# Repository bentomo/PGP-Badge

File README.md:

# Pokemon Go Plus Custom Badge

## Installing Toolchain

This was all tested under Windows 10

1. Install Python 2.7 (This is tested by 2.7.12)
	This is required for the edf-sdk installer

2. Install CMake for Windows (Tested using 3.17.0)

3. Install espressif SDK (Tested using Windows installer 2.2)
https://docs.espressif.com/projects/esp-idf/en/latest/get-started/#id1

I needed to use this because of an installer problem
https://github.com/espressif/esp-idf/issues/4744

`python.exe -m pip install --upgrade virtualenv==16.7.9`

Then run the program as administrator

## Extracting a MAC, Blob, and Key

Note that this is unusable without a Mac address, BLOB and device key from an **ORIGINAL** Pokemon GO plus
Pokeball plus and Gotcha not supported
https://github.com/Jesus805/Suota-Go-Plus

It's easiest to use the release page app 

Currently the app is bugged, it can download custom firmware but you need to use the  nRF android app to extract the values and restore the FW
MAC address is given by the app
characteristic `870d5ab1-20bd-b88a-5746-a97f5c33ea58` is the device key
characteristic `fe0002af-f8e3-f1b2-b141-b40adf381d18` is the blob

To restore the FW

1. Write 0x01 to Characteristic `6b64be6f-5467-d8b5-7143-1716be1b96be`
2. Disconnect from the device
3. Wait a few seconds
4. Press the Pokemon Go Plus button, it should be flashing blue or white

## Building the firmware

1. Open a command window
2. Browse to the esp-idf folder and run export.bat to setup sdk
3. Browse to the pgpemu-esp32 project folder and run `idf.py menuconfig`
4. Exit using the default configuration
5. Modify your secrets.c file with your MAC, Blob, and Key extracted from an original Pokemon GO Plus - This file is not tracked by git
6. Build the firmware using `idf.py build`
7. Flash the firmware using `idf.py -p (PORT) flash` where (PORT) is the COMX that the esp32 enumerated as

For more background read:
http://tinyhack.com/2018/11/21/reverse-engineering-pokemon-go-plus/

## Preliminary parts list
> ESP32 - Bluetooth - https://www.digikey.com/product-detail/en/espressif-systems/ESP32-WROOM-32/1904-1010-1-ND/8544305
> SSD1306 - OLED LCD - https://www.amazon.com/WINGONEER-Display-SSD1306-Headers-Arduino/dp/B07QB65CPS/ref=sr_1_5?keywords=oled+module&qid=1584226742&sr=8-5
> ~~ adafruit 1578 - 500mah battery - https://www.digikey.com/product-detail/en/adafruit-industries-llc/1578/1528-1841-ND/5054539 ~~
> battery - https://www.digikey.com/product-detail/en/tinycircuits/ASR00008/1832-1044-ND/8680974
> BQ27426 - Fuel Gauge - https://www.digikey.com/product-detail/en/texas-instruments/BQ27426YZFR/296-43359-1-ND/5806500
> LM3658 - Battery Charger - https://www.digikey.com/product-detail/en/texas-instruments/LM3658SD-NOPB/LM3658SD-NOPBCT-ND/808013
> TPS63030 - Voltage Regulator - https://www.digikey.com/product-detail/en/texas-instruments/TPS63030DSKR/296-39460-1-ND/5143408
> CP2102N - USB Interface - https://www.digikey.com/product-detail/en/silicon-labs/CP2102N-A01-GQFN20R/336-4826-1-ND/8619802
> USB4085 - Through hole usb c - https://www.digikey.com/product-detail/en/gct/USB4085-GF-A/2073-USB4085-GF-ACT-ND/9859733
> 316040004 - Vibration Motor - https://www.digikey.com/product-detail/en/seeed-technology-co-ltd/316040004/1597-1245-ND/5487673
> ~~ BQ297X - Protection Circuit - http://www.ti.com/lit/ds/symlink/bq2971.pdf ~ Battery includes protection circuit~

Other components not listed
jelly beans
sense resitors
tactile switches
mechanicals

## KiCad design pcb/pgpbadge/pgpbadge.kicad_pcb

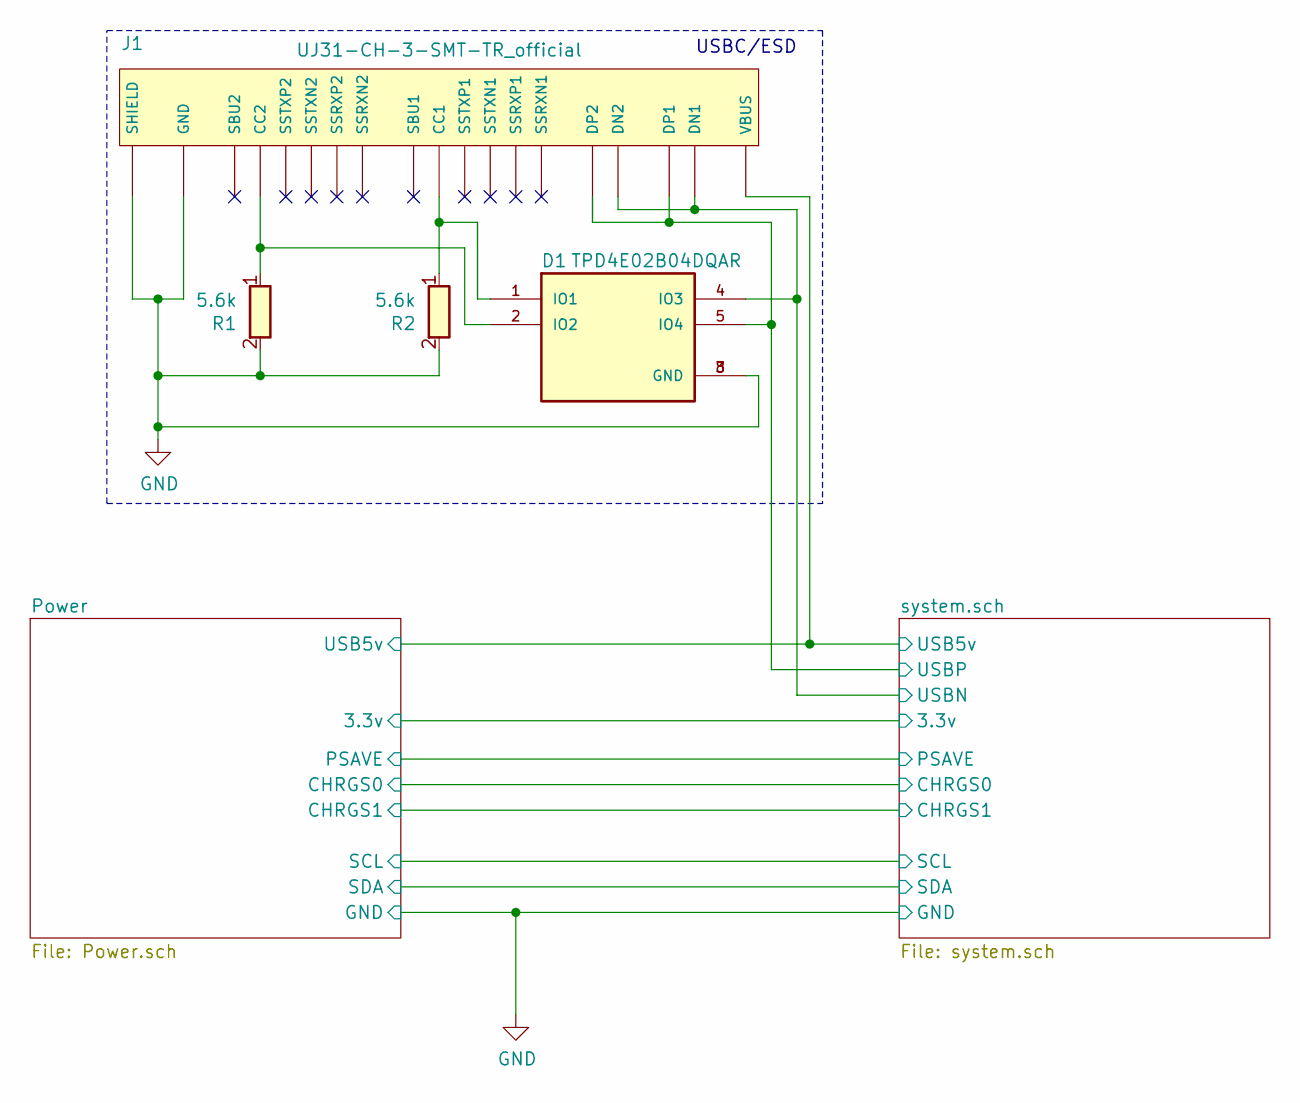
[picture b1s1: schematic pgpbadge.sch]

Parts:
D1: TPD4E02B04DQAR; DIO_TPD4E02B04DQAR
J1: UJ31-CH-3-SMT-TR_official; CUI_UJ31-CH-3-SMT-TR
R1, R2: 5.6k; R_0402_1005Metric

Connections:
/Power/USB5v: J1.A4 (VBUS), J1.A9 (VBUS), J1.B4 (VBUS), J1.B9 (VBUS); also elsewhere on the board
/system.sch/USBN: D1.4 (IO3), J1.A7 (DN1), J1.B7 (DN2); also elsewhere on the board
/system.sch/USBP: D1.5 (IO4), J1.A6 (DP1), J1.B6 (DP2); also elsewhere on the board
GND: D1.3 (GND), D1.8 (GND), J1.0 (SHIELD), J1.A1 (GND), J1.A12 (GND), J1.B1 (GND), J1.B12 (GND), R1.2, R2.2; also elsewhere on the board
unnamed: D1.1 (IO1), J1.A5 (CC1), R2.1
unnamed: D1.2 (IO2), J1.B5 (CC2), R1.1

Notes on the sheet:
USBC/ESD

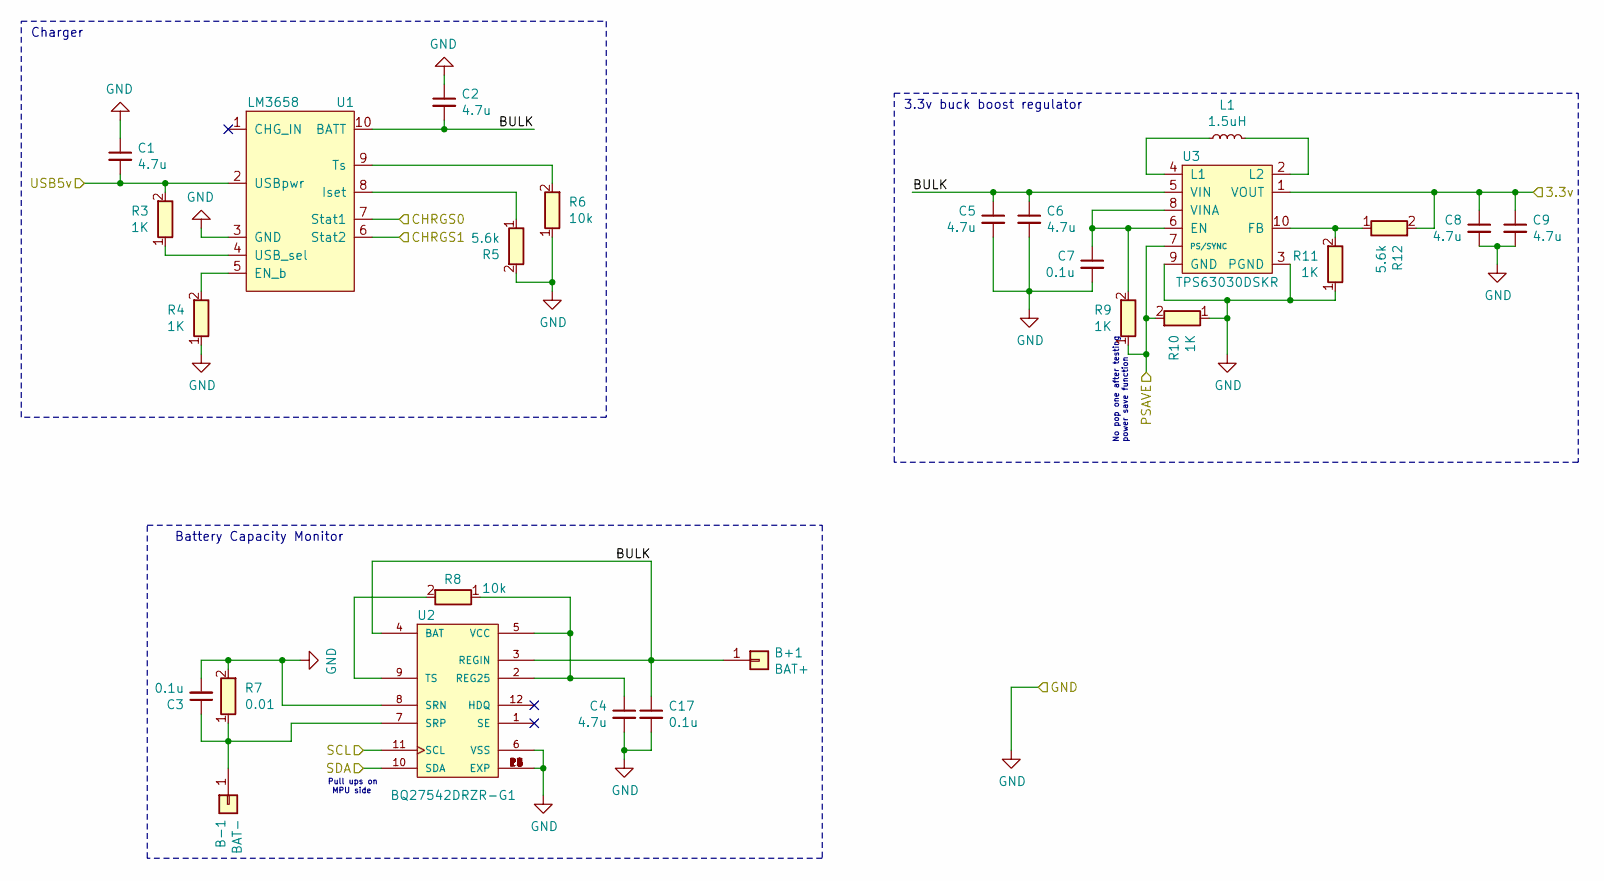
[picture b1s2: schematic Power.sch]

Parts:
B+1: BAT+; solder_pad
B-1: BAT-; solder_pad
C1, C2, C4, C5, C6, C8, C9: 4.7u; C_0805_2012Metric
C3, C7, C17: 0.1u; C_0402_1005Metric
L1: 1.5uH; L_1008_2520Metric
R3, R4, R9, R10, R11: 1K; R_0402_1005Metric
R5, R12: 5.6k; R_0402_1005Metric
R6, R8: 10k; R_0402_1005Metric
R7: 0.01; R_1206_3216Metric
U1: LM3658; wson-10-3x3
U2: BQ27542DRZR-G1; SON40P250X400X100-13N
U3: TPS63030DSKR; 10-WFDFN_EP_2.5_2.5

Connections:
/Power/BULK: B+1.1, C2.2, C5.1, C6.1, C17.1, U1.10 (BATT), U2.3 (REGIN), U2.4 (BAT), U3.5 (VIN)
/Power/CHRGS0: U1.7 (Stat1); also elsewhere on the board
/Power/CHRGS1: U1.6 (Stat2); also elsewhere on the board
/Power/PSAVE: R9.1, R10.2, U3.7 (PS/SYNC); also elsewhere on the board
/Power/SCL: U2.11 (SCL); also elsewhere on the board
/Power/SDA: U2.10 (SDA); also elsewhere on the board
/Power/USB5v: C1.2, R3.2, U1.2 (USBpwr); also elsewhere on the board
GND: C1.1, C2.1, C3.2, C4.2, C5.2, C6.2, C7.2, C8.2, C9.2, C17.2, R4.1, R5.2, R6.1, R7.2, R10.1, R11.1, U1.3 (GND), U2.6 (VSS), U2.8 (SRN), U2.13 (EXP), U2.14 (EXP), U2.15 (EXP), U2.P1 (EXP), U2.P2 (EXP), U2.P3 (EXP), U2.P4 (EXP), U2.P5 (EXP), U2.P6 (EXP), U3.3 (PGND), U3.9 (GND); also elsewhere on the board
unnamed: B-1.1, C3.1, R7.1, U2.7 (SRP)
unnamed: C4.1, R8.1, U2.2 (REG25), U2.5 (VCC)
unnamed: C7.1, R9.2, U3.6 (EN), U3.8 (VINA)
unnamed: L1.1, U3.4 (L1)
unnamed: L1.2, U3.2 (L2)
unnamed: R3.1, U1.4 (USB_sel)
unnamed: R4.2, U1.5 (EN_b)
unnamed: R5.1, U1.8 (Iset)
unnamed: R6.2, U1.9 (Ts)
unnamed: R8.2, U2.9 (TS)
unnamed: R11.2, R12.1, U3.10 (FB)

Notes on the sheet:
Pull ups on MPU side
No pop one after testing power save function
3.3v buck boost regulator
Battery Capacity Monitor
Charger

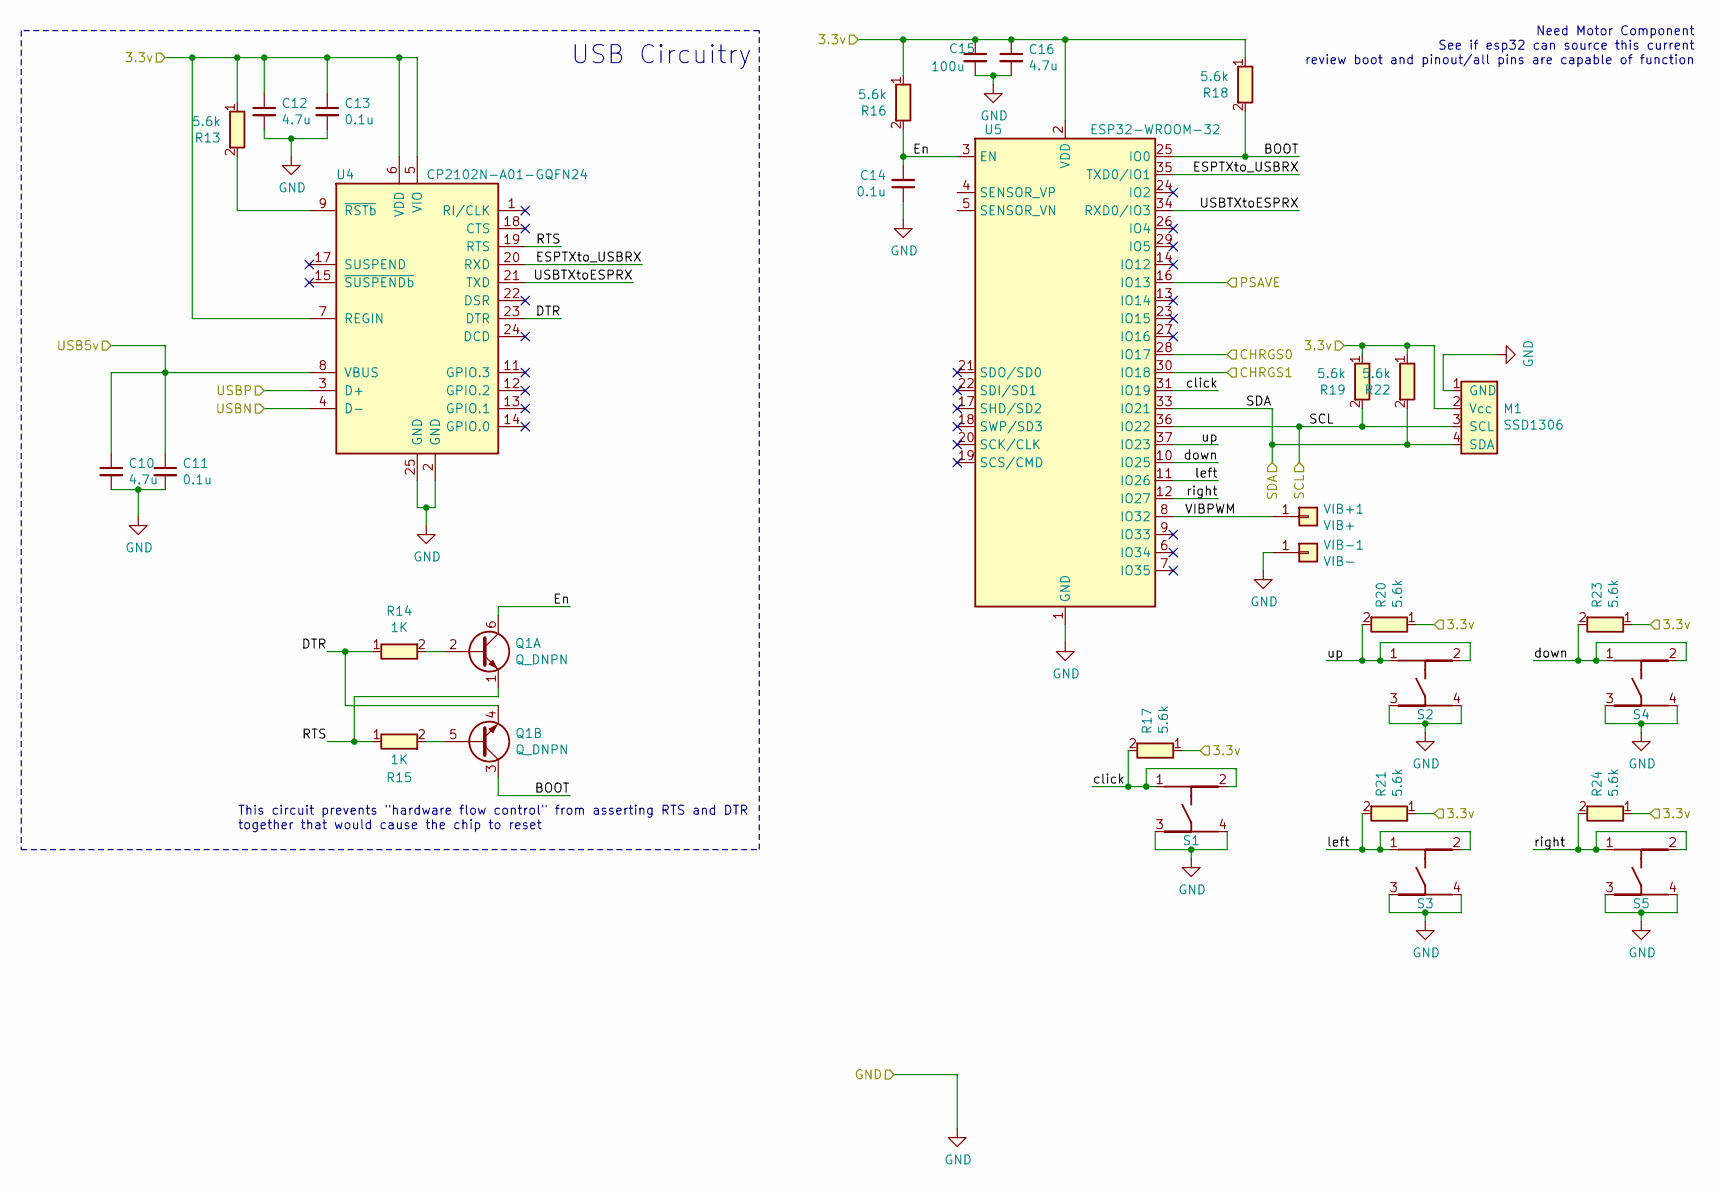
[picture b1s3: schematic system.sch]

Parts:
C10, C12, C16: 4.7u; C_0805_2012Metric
C11, C13, C14: 0.1u; C_0402_1005Metric
C15: 100u; C_1206_3216Metric
M1: SSD1306; ssd1306
Q1: Q_DNPN; SOT-363_SC-70-6
R13, R16, R17, R18, R19, R20, R21, R22, R23, R24: 5.6k; R_0402_1005Metric
R14, R15: 1K; R_0402_1005Metric
S1, S2, S3, S4, S5: tactile_TL3305AF160QG
U4: CP2102N-A01-GQFN24; QFN-24-1EP_4x4mm_P0.5mm_EP2.6x2.6mm
U5: ESP32-WROOM-32
VIB+1: VIB+; solder_pad
VIB-1: VIB-; solder_pad

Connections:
/Power/CHRGS0: U5.28 (IO17); also elsewhere on the board
/Power/CHRGS1: U5.30 (IO18); also elsewhere on the board
/Power/PSAVE: U5.16 (IO13); also elsewhere on the board
/Power/SCL: M1.3 (SCL), R19.2, U5.36 (IO22); also elsewhere on the board
/Power/SDA: M1.4 (SDA), R22.2, U5.33 (IO21); also elsewhere on the board
/Power/USB5v: C10.1, C11.1, U4.8 (VBUS); also elsewhere on the board
/system.sch/BOOT: Q1.3 (C2), R18.2, U5.25 (IO0)
/system.sch/DTR: Q1.4 (E2), R14.1, U4.23 (DTR)
/system.sch/ESPTXto_USBRX: U4.20 (RXD), U5.35 (TXD0/IO1)
/system.sch/En: C14.2, Q1.6 (C1), R16.2, U5.3 (EN)
/system.sch/RTS: Q1.1 (E1), R15.1, U4.19 (RTS)
/system.sch/USBN: U4.4 (D-); also elsewhere on the board
/system.sch/USBP: U4.3 (D+); also elsewhere on the board
/system.sch/USBTXtoESPRX: U4.21 (TXD), U5.34 (RXD0/IO3)
/system.sch/VIBPWM: U5.8 (IO32), VIB+1.1
/system.sch/click: R17.2, S1.1, S1.2, U5.31 (IO19)
/system.sch/down: R23.2, S4.1, S4.2, U5.10 (IO25)
/system.sch/left: R21.2, S3.1, S3.2, U5.11 (IO26)
/system.sch/right: R24.2, S5.1, S5.2, U5.12 (IO27)
/system.sch/up: R20.2, S2.1, S2.2, U5.37 (IO23)
GND: C10.2, C11.2, C12.2, C13.2, C14.1, C15.2, C16.2, M1.1 (GND), S1.3, S1.4, S2.3, S2.4, S3.3, S3.4, S4.3, S4.4, S5.3, S5.4, U4.2 (GND), U4.25 (GND), U5.1 (GND), U5.15 (GND), U5.38 (GND), U5.39 (GND), VIB-1.1; also elsewhere on the board
unnamed: Q1.2 (B1), R14.2
unnamed: Q1.5 (B2), R15.2

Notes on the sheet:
This circuit prevents "hardware flow control" from asserting RTS and DTR together that would cause the chip to reset
USB Circuitry
Need Motor Component See if esp32 can source this current review boot and pinout/all pins are capable of function

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
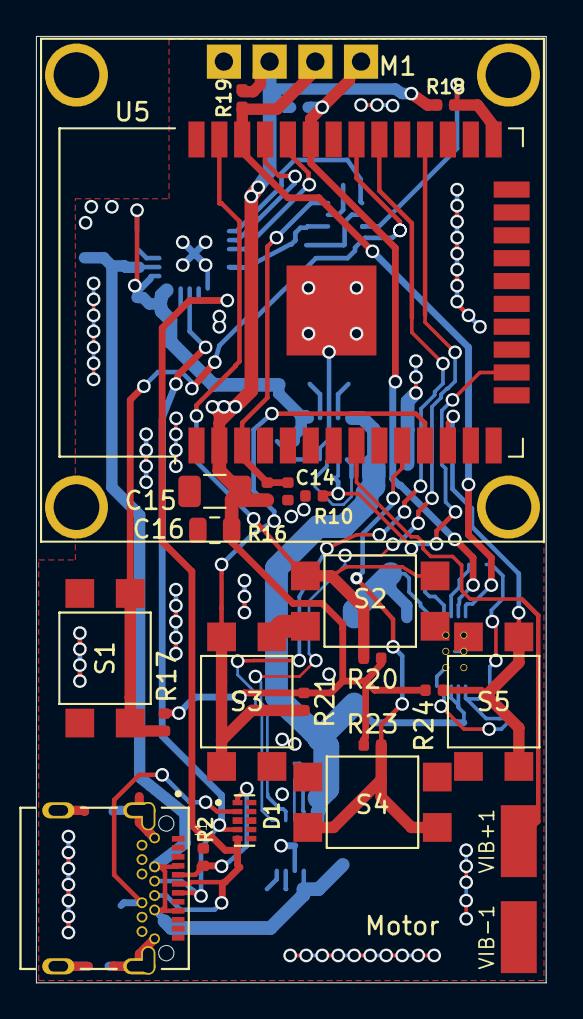
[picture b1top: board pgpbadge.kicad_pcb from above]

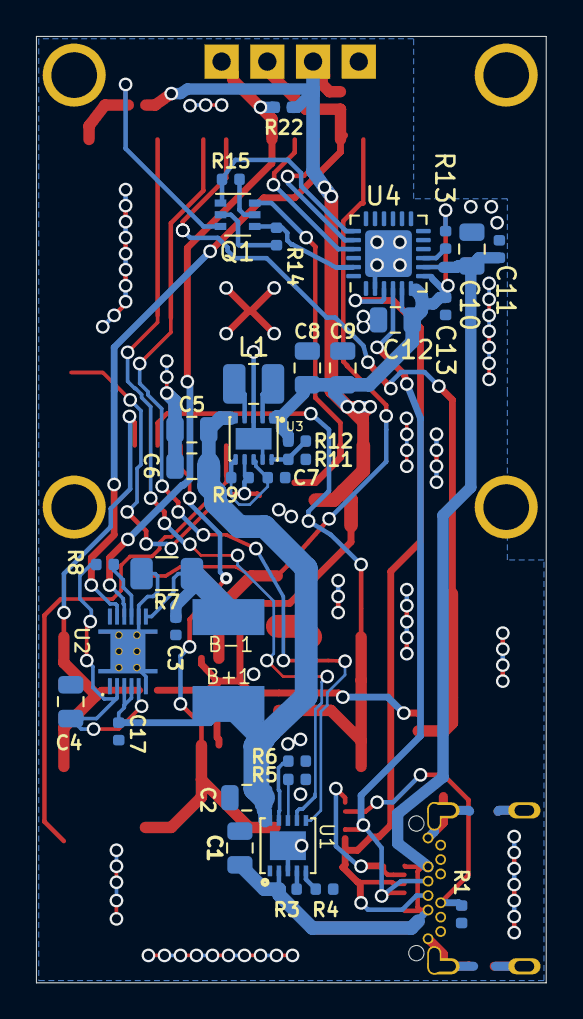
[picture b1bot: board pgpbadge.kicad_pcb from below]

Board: 4 copper layers, 28.3 x 52.6 mm, 60 parts (36 on the bottom side), 39 nets.

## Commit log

2020-04-05 Base build working, schematic entry nearing completion
2020-05-04 Board layout and routing done, need to fix DRC's, add more ground stitching, clean up silscreen, and review
2020-05-07 Fixed DRCs except USB C
2020-05-09 DRC's clean, silscreen updated, 1ks changed to 5.6k
